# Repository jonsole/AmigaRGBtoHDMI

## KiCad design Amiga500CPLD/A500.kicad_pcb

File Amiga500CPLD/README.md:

# Amiga 500 CPLD RGBtoHDMI

This adaptor uses a CPLD to pass the RGB and sync signals from the Amiga 500 Denise socket to the Rasperry Pi Zero. It derives the pixel clock in a very different way to the c0pperdragon design and therefore does not require a jumper for Denise / Super Denise and has no "sparkling" pixel issues. It also has the advantage of being firmware upgradable if there are any issues found in the logic.

**ATTENTION PI Zero 2W users**: You can now use a Pi Zero 2W with the CPLD RGBtoHDMI using the December 24th 2021 release.

## BOM

| Symbol     | Component                         |
| ---------- | --------------------------------- |
| C1 - C3    | 0.1uF 0603                        |
| J1         | 2x20pin 16.5mm tall socket 2.54mm |
| JP1        | 2pin right angle header 2.54mm    |
| J2         | 1pin right angle header 2.54mm    |
| R1         | 1K 0603                           |
| R2         | 4.7K 0603                         |
| U1         | 48pin DIP socket 2.54mm           |
| U2         | 2x24pin SILs machined pins 2.54mm |
| U3         | XC9572XL 44pin QFP                |

### Notes

- It is important that R1 is 1K due to the low value of the internal pull resistor in GPIO0 of the Pi, the other pull resistors are more flexible (R1 is optional as the Pi will pull this internally). If the value is too high then the software won't detect this is an Amiga board and won't show the correct firmware in the recovery menu.
- You'll need some kind of push button to connect to JP1
- J2 is optional, it is only needed for revision 3 motherboards to clip onto pin 9 of U41 on the Amiga (photo coming soon)
- The Pi mounting holes are M2.5, 11mm posts or 10mm with 1mm washers are recommended

## Pi Software Installation

The software on the Pi should be at least the latest 20210529 release from the [main tree](https://github.com/hoglet67/RGBtoHDMI/releases) or the latest [IanSB beta release](https://github.com/IanSB/RGBtoHDMI/releases) extracted onto a micro SD card in FAT32 format.

You need to copy some canned profile files into place for the board:

* `Amiga_CPLD_Readme/Amiga_CPLD_Setup/profile_6-12_BIT_RGB.txt` to the root of the SD card
* `Amiga_CPLD_Readme/Amiga_CPLD_Setup/Profiles/Default.txt` to the `Profiles` directory

This resolves some issues with mode switching, particularly on NTSC machines. The profile copied will automatically set `single_button_mode`.

## Flashing the CPLD

The CPLD will need flashing with the `6-12_BIT_RGB_CPLD` firmware. The other firmware options are not compatible with the profiles.

If you have followed the software steps above you will get a recovery menu, select `6-12_BIT_RGB_CPLD`, confirm and the Pi will flash the CPLD and reboot. You can then jump to the Initial Setup section below.

## Initial Setup

You may also a shimmer or wavy effect. This is because the phase is set incorrectly and needs calibration, this is a one-off easy thing to do. If you have a static image such as the Kickstart 1.3 boot screen or Workbench with no mouse movement you can use the "Auto Calibrate Video Settings" option (it will require you to select twice to activate). Alternatively you can go into the "Sampling" menu and change the "Sampling Phase" until the image looks correct. Typically 0, 3 or 5 will work fine, but it could be different in each machine.

Once calibrated choose "Save Configuration" and this will be remembered for subsequent boots.

## Buying PCBs

I've made the [PCBs available on PCBWay](https://www.pcbway.com/project/shareproject/Amiga_500_CPLD_RGBtoHDMI_v2_fb52eff9.html).

You can also purchase PCBs from me [via Tindie](https://www.tindie.com/products/linuxjedi/amiga-500-rgb-to-hdmi-pcb/).

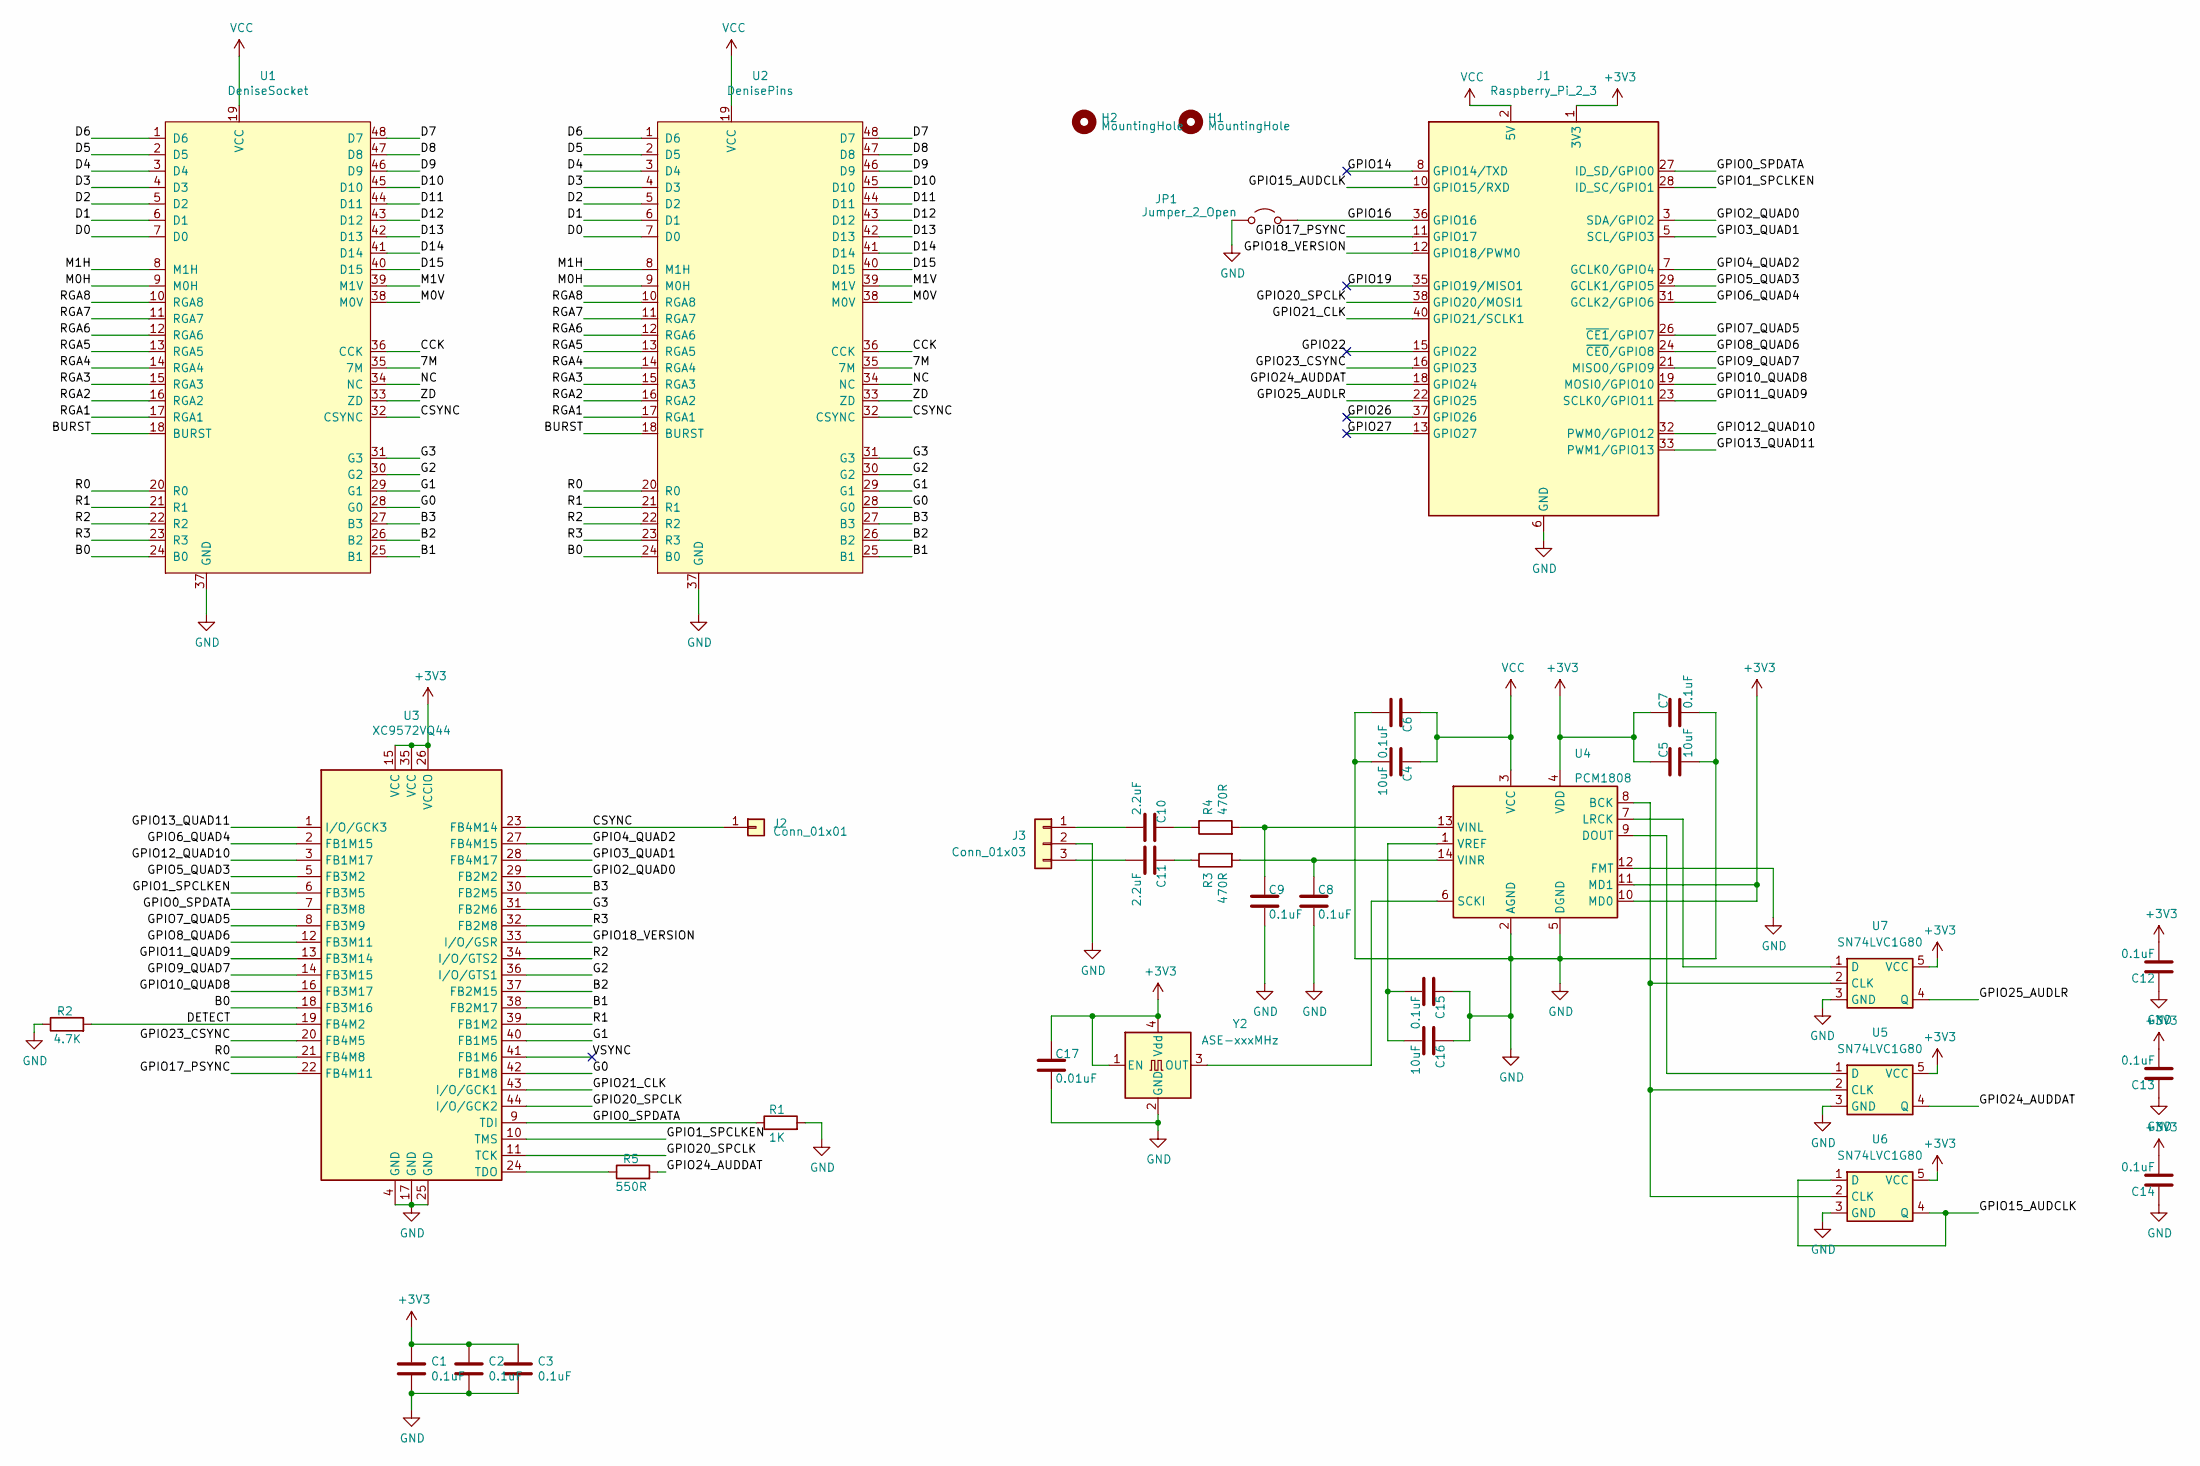
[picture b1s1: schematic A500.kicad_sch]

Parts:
C1, C2, C3, C6, C7, C8, C9, C12, C13, C14, C15: 0.1uF; C_0603_1608Metric_Pad1.08x0.95mm_HandSolder
C4, C5, C16: 10uF; C_0805_2012Metric_Pad1.18x1.45mm_HandSolder
C10, C11: 2.2uF; C_0805_2012Metric_Pad1.18x1.45mm_HandSolder
C17: 0.01uF; C_0603_1608Metric_Pad1.08x0.95mm_HandSolder
H1, H2: MountingHole; MountingHole_2.5mm_Pad
J1: Raspberry_Pi_2_3; Raspberry_Pi_Zero_Socketed_THT_FaceDown_MountingHoles
J2: Conn_01x01; PinHeader_1x01_P2.54mm_Horizontal
J3: Conn_01x03; PinHeader_1x03_P2.54mm_Horizontal
JP1: Jumper_2_Open; PinHeader_1x02_P2.54mm_Horizontal
R1: 1K; R_0603_1608Metric_Pad0.98x0.95mm_HandSolder
R2: 4.7K; R_0603_1608Metric_Pad0.98x0.95mm_HandSolder
R3, R4: 470R; R_0603_1608Metric_Pad0.98x0.95mm_HandSolder
R5: 550R; R_0603_1608Metric_Pad0.98x0.95mm_HandSolder
U1: DeniseSocket; DIP-48_W15.24mm_LongPads
U2: DenisePins; DIP-48_W15.24mm_LongPads
U3: XC9572VQ44; TQFP-44_10x10mm_P0.8mm
U4: PCM1808; TSSOP-14_4.4x5mm_P0.65mm
U5, U6, U7: SN74LVC1G80; Texas_R-PDSO-G5_DCK-5
Y2: ASE-xxxMHz; Oscillator_SMD_Abracon_ASE-4Pin_3.2x2.5mm

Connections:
+3V3: C1.1, C2.1, C3.1, C5.1, C7.1, C12.2, C13.2, C14.2, C17.1, J1.1 (3V3), J1.17 (3V3), U3.15 (VCC), U3.26 (VCCIO), U3.35 (VCC), U4.4 (VDD), U4.10 (MD0), U4.11 (MD1), U5.5 (VCC), U6.5 (VCC), U7.5 (VCC), Y2.1 (EN), Y2.4 (Vdd)
/7M: U1.35 (7M), U2.35 (7M)
/B0: U1.24 (B0), U2.24 (B0), U3.18 (FB3M16)
/B1: U1.25 (B1), U2.25 (B1), U3.38 (FB2M17)
/B2: U1.26 (B2), U2.26 (B2), U3.37 (FB2M15)
/B3: U1.27 (B3), U2.27 (B3), U3.30 (FB2M5)
/BURST: U1.18 (BURST), U2.18 (BURST)
/CCK: U1.36 (CCK), U2.36 (CCK)
/CSYNC: J2.1, U1.32 (CSYNC), U2.32 (CSYNC), U3.23 (FB4M14)
/D0: U1.7 (D0), U2.7 (D0)
/D1: U1.6 (D1), U2.6 (D1)
/D2: U1.5 (D2), U2.5 (D2)
/D3: U1.4 (D3), U2.4 (D3)
/D4: U1.3 (D4), U2.3 (D4)
/D5: U1.2 (D5), U2.2 (D5)
/D6: U1.1 (D6), U2.1 (D6)
/D7: U1.48 (D7), U2.48 (D7)
/D8: U1.47 (D8), U2.47 (D8)
/D9: U1.46 (D9), U2.46 (D9)
/D10: U1.45 (D10), U2.45 (D10)
/D11: U1.44 (D11), U2.44 (D11)
/D12: U1.43 (D12), U2.43 (D12)
/D13: U1.42 (D13), U2.42 (D13)
/D14: U1.41 (D14), U2.41 (D14)
/D15: U1.40 (D15), U2.40 (D15)
/DETECT: R2.2, U3.19 (FB4M2)
/G0: U1.28 (G0), U2.28 (G0), U3.42 (FB1M8)
/G1: U1.29 (G1), U2.29 (G1), U3.40 (FB1M5)
/G2: U1.30 (G2), U2.30 (G2), U3.36 (I/O/GTS1)
/G3: U1.31 (G3), U2.31 (G3), U3.31 (FB2M6)
/GPIO0_SPDATA: J1.27 (ID_SD/GPIO0), R1.1, U3.7 (FB3M8), U3.9 (TDI)
/GPIO1_SPCLKEN: J1.28 (ID_SC/GPIO1), U3.6 (FB3M5), U3.10 (TMS)
/GPIO2_QUAD0: J1.3 (SDA/GPIO2), U3.29 (FB2M2)
/GPIO3_QUAD1: J1.5 (SCL/GPIO3), U3.28 (FB4M17)
/GPIO4_QUAD2: J1.7 (GCLK0/GPIO4), U3.27 (FB4M15)
/GPIO5_QUAD3: J1.29 (GCLK1/GPIO5), U3.5 (FB3M2)
/GPIO6_QUAD4: J1.31 (GCLK2/GPIO6), U3.2 (FB1M15)
/GPIO7_QUAD5: J1.26 (~CE1/GPIO7), U3.8 (FB3M9)
/GPIO8_QUAD6: J1.24 (~CE0/GPIO8), U3.12 (FB3M11)
/GPIO9_QUAD7: J1.21 (MISO0/GPIO9), U3.14 (FB3M15)
/GPIO10_QUAD8: J1.19 (MOSI0/GPIO10), U3.16 (FB3M17)
/GPIO11_QUAD9: J1.23 (SCLK0/GPIO11), U3.13 (FB3M14)
/GPIO12_QUAD10: J1.32 (PWM0/GPIO12), U3.3 (FB1M17)
/GPIO13_QUAD11: J1.33 (PWM1/GPIO13), U3.1 (I/O/GCK3)
/GPIO14: J1.8 (GPIO14/TXD)
/GPIO15_AUDCLK: J1.10 (GPIO15/RXD), U6.1 (D), U6.4 (Q)
/GPIO16: J1.36 (GPIO16), JP1.2 (B)
/GPIO17_PSYNC: J1.11 (GPIO17), U3.22 (FB4M11)
/GPIO18_VERSION: J1.12 (GPIO18/PWM0), U3.33 (I/O/GSR)
/GPIO19: J1.35 (GPIO19/MISO1)
/GPIO20_SPCLK: J1.38 (GPIO20/MOSI1), U3.11 (TCK), U3.44 (I/O/GCK2)
/GPIO21_CLK: J1.40 (GPIO21/SCLK1), U3.43 (I/O/GCK1)
/GPIO22: J1.15 (GPIO22)
/GPIO23_CSYNC: J1.16 (GPIO23), U3.20 (FB4M5)
/GPIO24_AUDDAT: J1.18 (GPIO24), R5.2, U5.4 (Q)
/GPIO25_AUDLR: J1.22 (GPIO25), U7.4 (Q)
/GPIO26: J1.37 (GPIO26)
/GPIO27: J1.13 (GPIO27)
/M0H: U1.9 (M0H), U2.9 (M0H)
/M0V: U1.38 (M0V), U2.38 (M0V)
/M1H: U1.8 (M1H), U2.8 (M1H)
/M1V: U1.39 (M1V), U2.39 (M1V)
/NC: U1.34 (NC), U2.34 (NC)
/R0: U1.20 (R0), U2.20 (R0), U3.21 (FB4M8)
/R1: U1.21 (R1), U2.21 (R1), U3.39 (FB1M2)
/R2: U1.22 (R2), U2.22 (R2), U3.34 (I/O/GTS2)
/R3: U1.23 (R3), U2.23 (R3), U3.32 (FB2M8)
/RGA1: U1.17 (RGA1), U2.17 (RGA1)
/RGA2: U1.16 (RGA2), U2.16 (RGA2)
/RGA3: U1.15 (RGA3), U2.15 (RGA3)
/RGA4: U1.14 (RGA4), U2.14 (RGA4)
/RGA5: U1.13 (RGA5), U2.13 (RGA5)
/RGA6: U1.12 (RGA6), U2.12 (RGA6)
/RGA7: U1.11 (RGA7), U2.11 (RGA7)
/RGA8: U1.10 (RGA8), U2.10 (RGA8)
/VSYNC: U3.41 (FB1M6)
/ZD: U1.33 (ZD), U2.33 (ZD)
GND: C1.2, C2.2, C3.2, C4.2, C5.2, C6.2, C7.2, C8.2, C9.2, C12.1, C13.1, C14.1, C15.1, C16.1, C17.2, J1.6 (GND), J1.9 (GND), J1.14 (GND), J1.20 (GND), J1.25 (GND), J1.30 (GND), J1.34 (GND), J1.39 (GND), J3.2, JP1.1 (A), R1.2, R2.1, U1.37 (GND), U2.37 (GND), U3.4 (GND), U3.17 (GND), U3.25 (GND), U4.2 (AGND), U4.5 (DGND), U4.12 (FMT), U5.3 (GND), U6.3 (GND), U7.3 (GND), Y2.2 (GND)
unnamed: C10.1, R4.1
unnamed: C11.1, R3.1
unnamed: C10.2, J3.1
unnamed: C11.2, J3.3
unnamed: R5.1, U3.24 (TDO)
unnamed: U4.8 (BCK), U5.2 (CLK), U6.2 (CLK), U7.2 (CLK)
unnamed: U4.9 (DOUT), U5.1 (D)
unnamed: U4.7 (LRCK), U7.1 (D)
unnamed: U4.6 (SCKI), Y2.3 (OUT)
unnamed: C9.1, R4.2, U4.13 (VINL)
unnamed: C8.1, R3.2, U4.14 (VINR)
unnamed: C15.2, C16.2, U4.1 (VREF)
VCC: C4.1, C6.1, J1.2 (5V), J1.4 (5V), U1.19 (VCC), U2.19 (VCC), U4.3 (VCC)

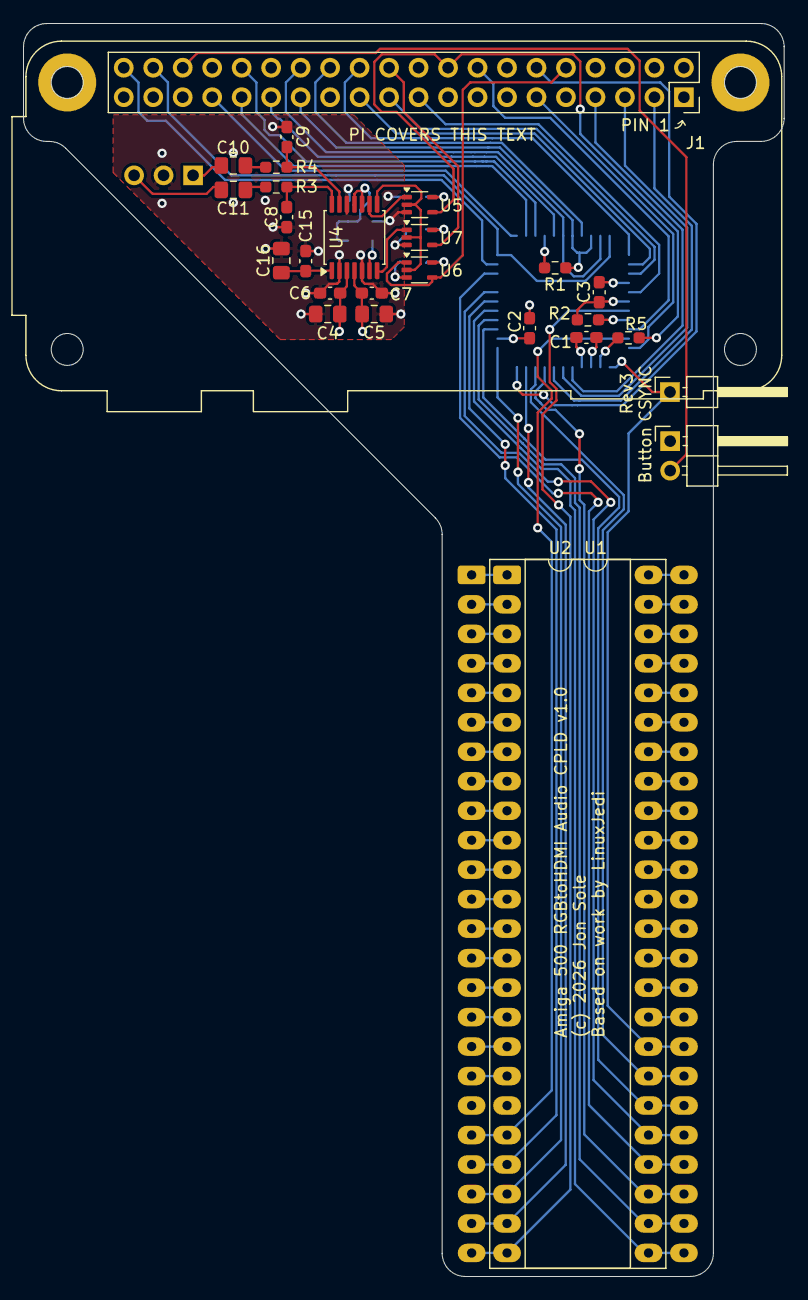
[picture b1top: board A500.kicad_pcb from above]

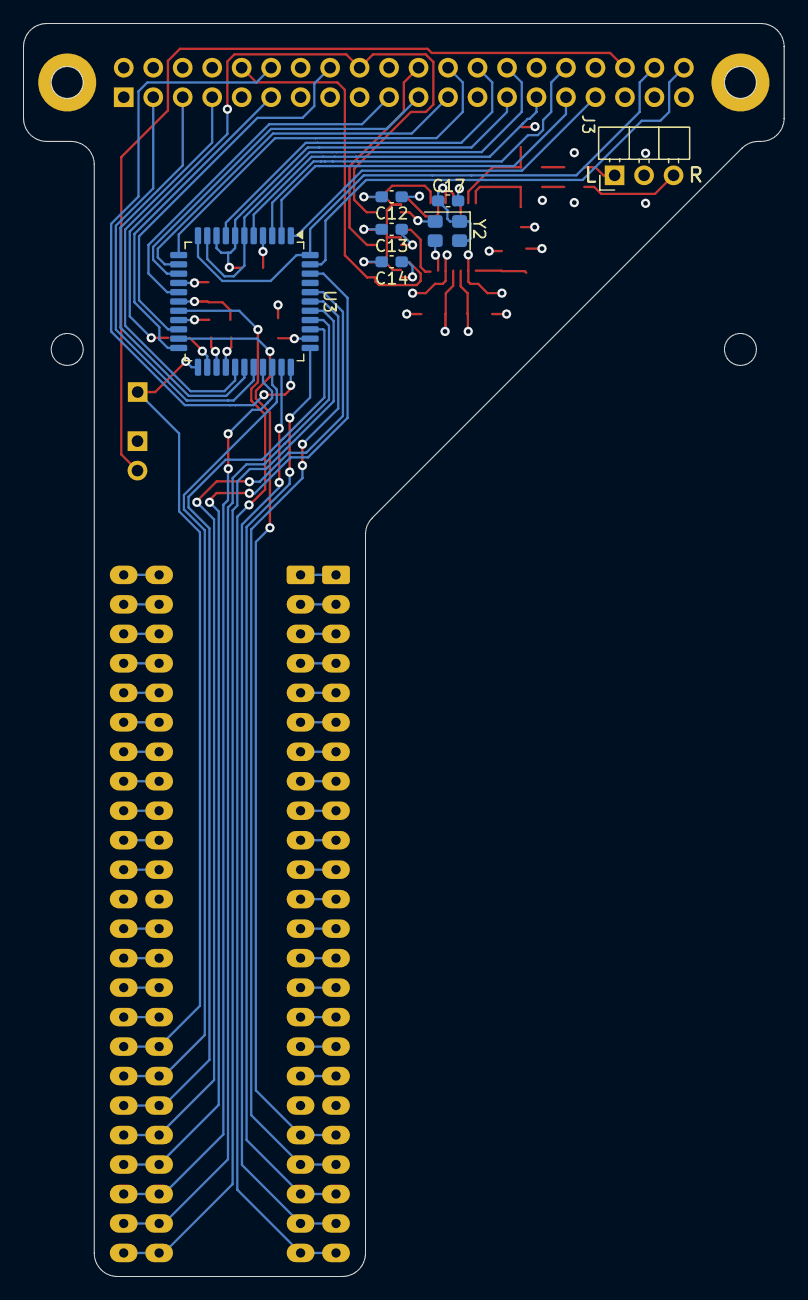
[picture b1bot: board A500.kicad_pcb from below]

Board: 4 copper layers, 65.5 x 108.0 mm, 36 parts (7 on the bottom side), 85 nets.

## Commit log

2026-03-18 Update design to include audio
2026-03-20 Remove old files
2026-03-20 Update PI header in readme

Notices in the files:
Amiga500CPLD/A500.kicad_pcb:
(c) 2026 Jon Sole
